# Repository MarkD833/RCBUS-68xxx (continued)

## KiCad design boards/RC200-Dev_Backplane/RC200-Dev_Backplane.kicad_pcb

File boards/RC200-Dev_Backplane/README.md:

# RCBus-80 Backplane

# Details
This is my offering of an RCBus-80 backplane. In the past I have used Steve Cousins SC701 6-slot backplanes for my boards. However, I found that at 6 slots, I might run out slots.

I had a chat with Steve to get his approval for me to take his SC701 backplane design and alter it for my own needs.

This backplane I've put together has 2 additional slots - making 8 in total. It also incorporates parts of Steve's SC719 digital I/O board to give 8 debug LEDs and 8 tactile pushbuttons. I also incorporated his SC729 CompactFlash module (with electronics by Tadeusz Pycio - www.vtsys.pl) as well.

The downside is that there is no expansion RCBus-80 connector to extend the bus further.

As well as combining Steve's SC701, SC719 and SC729 into one board, I've also added an LED driven by the /HALT signal buffered by one of the spare 74LS32 OR gates.

**NOTE** There is no voltage regulator on this board - an externally regulated 5V supply is required. Further, there is **NO** reverse polarity protection so check your power supply polarity.

# Board Assembly
Assembly of the board should be fairly straightforward. There are no surface mount devices to deal with.

Note regarding C18 - the capacitor is rather close to the pins that poke out the back of a board fitted to slot 8. Either use a standard height 100uF capacitor and bend the legs to 90 degrees so it sits horizontal to the board or use one of the lower profile capacitors that are around 7mm or 8mm tall.

Depending on your choice of LED colours, the associated current limiting resistor may need to be altered to give visually similar brightnesses.

# CompactFlash Adapter Header
The 2x20 header for the CompactFlash adapter can be a standard 2x20 0.1in (2.54mm) pin header or you can use a 2x20 shrouded IDC connector with ejector levers. The latter provides keying to avoid inserting the CompactFlash adapter the wrong way round and ejector levers to avoid bending pins.

# Jumpers
I have tried to replicate the jumper configurations that Steve provides on his SC701 so please refer to his documentation.

For my RCBus-68000, pinheaders J9..J22 should all have jumpers fitted to allow all signals to pass through. 

J23 should normally have a jumper fitted to connect the DS1233 reset signal to the backplane.

J24 can be used to provide an off-board reset switch if needed.
 
# Future Enhancements
+ Connect backplane D8..D15 to D8..D15 of the CompactFlash adapter to potentially allow for 16-bit data transfers.

# Errors
+ C18 - depending on the height of this capacitor, you may find it isn't possible to fully insert a board into the last backplane slot without bending the capacitor out of the way slightly.

# History
+ v1.0 - initial design

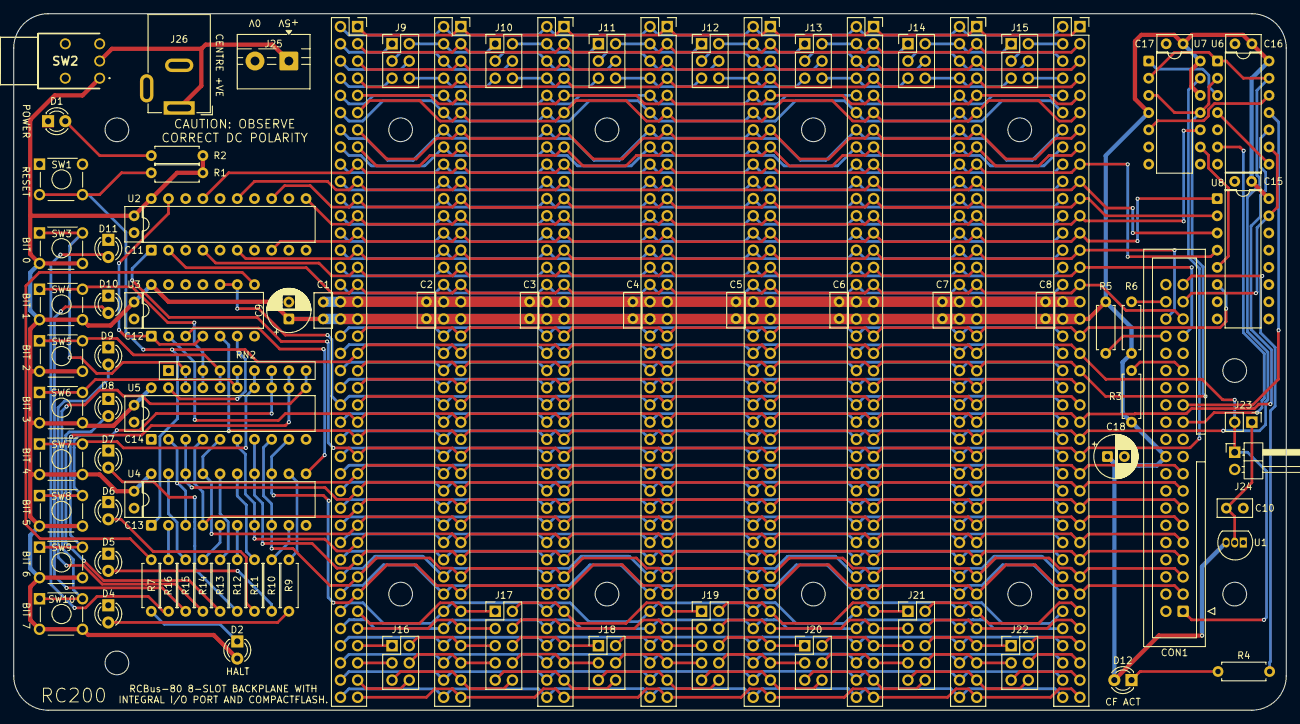
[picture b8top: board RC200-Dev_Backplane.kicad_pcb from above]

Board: 2 copper layers, 188.0 x 102.9 mm, 102 parts (0 on the bottom side), 170 nets.

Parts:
C1, C2, C3, C4, C5, C6, C7, C8, C11, C12, C13, C14, C15, C16, C17: 100n; C_Disc_D5.0mm_W2.5mm_P2.50mm
C9, C18: 100uF; CP_Radial_D6.3mm_P2.50mm
C10: 1n; C_Disc_D5.0mm_W2.5mm_P2.50mm
CON1: CONN_IDE_02x20; IDC-Header_2x20_P2.54mm_Vertical
D1, D2, D4, D5, D6, D7, D8, D9, D10, D11, D12: LED; LED_D3.0mm
H1, H2, H3, H4, H5, H6, H7, H8, H9, H10, H11, H12: MountingHole; MountingHole_3.5mm
J1, J2, J3, J4, J5, J6, J7, J8: Conn_02x40_Top_Bottom; PinSocket_2x40_P2.54mm_Vertical_Top_Bottom
J9, J10, J11, J12, J13, J14, J15, J16, J18, J20, J22: Conn_02x03_Odd_Even; PinHeader_2x03_P2.54mm_Vertical
J17, J19, J21: Conn_02x05_Odd_Even; PinHeader_2x05_P2.54mm_Vertical
J23: Conn_01x02; PinHeader_1x02_P2.54mm_Vertical
J24: Conn_01x02; PinHeader_1x02_P2.54mm_Horizontal
J25: Conn_01x02; TerminalBlock_MaiXu_MX126-5.0-02P_1x02_P5.00mm
J26: Barrel_Jack_Switch; BarrelJack_GCT_DCJ200-10-A_Horizontal
R1: 10K; R_Axial_DIN0207_L6.3mm_D2.5mm_P7.62mm_Horizontal
R2, R4, R7, R9, R10, R11, R12, R13, R14, R15, R16: 1K; R_Axial_DIN0207_L6.3mm_D2.5mm_P7.62mm_Horizontal
R3, R5, R6: 4K7; R_Axial_DIN0207_L6.3mm_D2.5mm_P7.62mm_Horizontal
RN2: 1K; R_Array_SIP9
SW1, SW3, SW4, SW5, SW6, SW7, SW8, SW9, SW10: SW_Push; SW_TH_Tactile
SW2: SW_SPDT; 2MS1T2B2M6QES
U1: DS1233-10; TO-92L_Inline
U2: 74HCT688; DIP-20_W7.62mm
U3, U6: 74LS32; DIP-14_W7.62mm
U4: 74HCT273; DIP-20_W7.62mm
U5: 74LS245; DIP-20_W7.62mm
U7: 74LS74; DIP-14_W7.62mm
U8: 74LS138; DIP-16_W7.62mm

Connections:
+5V: C1.1, C2.1, C3.1, C4.1, C5.1, C6.1, C7.1, C8.1, C9.1, C11.2, C12.2, C13.2, C14.2, C15.2, C16.2, C17.2, C18.1, CON1.20 (KEY), D2.2 (A), D12.2 (A), J1.18, J1.58, J2.18, J2.58, J3.18, J3.58, J4.18, J4.58, J5.18, J5.58, J6.18, J6.58, J7.18, J7.58, J8.18, J8.58, R1.1, R2.1, R3.1, R5.1, R6.1, SW2.1 (A), SW3.2, SW4.2, SW5.2, SW6.2, SW7.2, SW8.2, SW9.2, SW10.2, U1.3 (VCC), U2.20 (VCC), U3.14 (VCC), U4.20 (VCC), U5.20 (VCC), U6.14 (VCC), U7.4 (~S), U7.12 (D), U7.14 (VCC), U8.16 (VCC)
/A0: CON1.35 (DA0), J1.16, J2.16, J3.16, J4.16, J5.16, J6.16, J7.16, J8.16, U2.2 (P0)
/A1: CON1.33 (DA1), J1.15, J2.15, J3.15, J4.15, J5.15, J6.15, J7.15, J8.15, U2.4 (P1)
/A2: CON1.36 (DA2), J1.14, J2.14, J3.14, J4.14, J5.14, J6.14, J7.14, J8.14, U2.6 (P2)
/A3: J1.13, J2.13, J3.13, J4.13, J5.13, J6.13, J7.13, J8.13, U2.8 (P3), U8.1 (A0)
/A4: J1.12, J2.12, J3.12, J4.12, J5.12, J6.12, J7.12, J8.12, U2.11 (P4), U7.10 (~S)
/A5: J1.11, J2.11, J3.11, J4.11, J5.11, J6.11, J7.11, J8.11, U2.13 (P5), U8.2 (A1)
/A6: J1.10, J2.10, J3.10, J4.10, J5.10, J6.10, J7.10, J8.10, U2.15 (P6), U8.3 (A2)
/A7: J1.9, J2.9, J3.9, J4.9, J5.9, J6.9, J7.9, J8.9, U2.17 (P7), U8.4 (E1)
/A8: J1.8, J2.8, J3.8, J4.8, J5.8, J6.8, J7.8, J8.8
/A9: J1.7, J2.7, J3.7, J4.7, J5.7, J6.7, J7.7, J8.7
/A10: J1.6, J2.6, J3.6, J4.6, J5.6, J6.6, J7.6, J8.6
/A11: J1.5, J2.5, J3.5, J4.5, J5.5, J6.5, J7.5, J8.5
/A12: J1.4, J2.4, J3.4, J4.4, J5.4, J6.4, J7.4, J8.4
/A13: J1.3, J2.3, J3.3, J4.3, J5.3, J6.3, J7.3, J8.3
/A14: J1.2, J2.2, J3.2, J4.2, J5.2, J6.2, J7.2, J8.2
/A15: J1.1, J2.1, J3.1, J4.1, J5.1, J6.1, J7.1, J8.1
/A16: J1.56, J2.56, J3.56, J4.56, J5.56, J6.56, J7.56, J8.56
/A17: J1.55, J2.55, J3.55, J4.55, J5.55, J6.55, J7.55, J8.55
/A18: J1.54, J2.54, J3.54, J4.54, J5.54, J6.54, J7.54, J8.54
/A19: J1.53, J2.53, J3.53, J4.53, J5.53, J6.53, J7.53, J8.53
/A20: J1.52, J2.52, J3.52, J4.52, J5.52, J6.52, J7.52, J8.52
/A21: J1.51, J2.51, J3.51, J4.51, J5.51, J6.51, J7.51, J8.51
/A22: J1.50, J2.50, J3.50, J4.50, J5.50, J6.50, J7.50, J8.50
/A23: J1.49, J2.49, J3.49, J4.49, J5.49, J6.49, J7.49, J8.49
/CLK: J1.21, J2.21, J3.21, J4.21, J5.21, J6.21, J7.21, J8.21, U6.2, U7.3 (C), U7.11 (C)
/CLK2: J1.61, J2.61, J3.61, J4.61, J5.61, J6.61, J7.61, J8.61
/D0: CON1.17 (D0), J1.27, J2.27, J3.27, J4.27, J5.27, J6.27, J7.27, J8.27, U4.3 (D0), U5.2 (A0)
/D1: CON1.15 (D1), J1.28, J2.28, J3.28, J4.28, J5.28, J6.28, J7.28, J8.28, U4.18 (D7), U5.3 (A1)
/D2: CON1.13 (D2), J1.29, J2.29, J3.29, J4.29, J5.29, J6.29, J7.29, J8.29, U4.4 (D1), U5.4 (A2)
/D3: CON1.11 (D3), J1.30, J2.30, J3.30, J4.30, J5.30, J6.30, J7.30, J8.30, U4.17 (D6), U5.5 (A3)
/D4: CON1.9 (D4), J1.31, J2.31, J3.31, J4.31, J5.31, J6.31, J7.31, J8.31, U4.7 (D2), U5.6 (A4)
/D5: CON1.7 (D5), J1.32, J2.32, J3.32, J4.32, J5.32, J6.32, J7.32, J8.32, U4.14 (D5), U5.7 (A5)
/D6: CON1.5 (D6), J1.33, J2.33, J3.33, J4.33, J5.33, J6.33, J7.33, J8.33, U4.8 (D3), U5.8 (A6)
/D7: CON1.3 (D7), J1.34, J2.34, J3.34, J4.34, J5.34, J6.34, J7.34, J8.34, U4.13 (D4), U5.9 (A7)
/D8: J1.67, J2.67, J3.67, J4.67, J5.67, J6.67, J7.67, J8.67
/D9: J1.68, J2.68, J3.68, J4.68, J5.68, J6.68, J7.68, J8.68
/D10: J1.69, J2.69, J3.69, J4.69, J5.69, J6.69, J7.69, J8.69
/D11: J1.70, J2.70, J3.70, J4.70, J5.70, J6.70, J7.70, J8.70
/D12: J1.71, J2.71, J3.71, J4.71, J5.71, J6.71, J7.71, J8.71
/D13: J1.72, J2.72, J3.72, J4.72, J5.72, J6.72, J7.72, J8.72
/D14: J1.73, J2.73, J3.73, J4.73, J5.73, J6.73, J7.73, J8.73
/D15: J1.74, J2.74, J3.74, J4.74, J5.74, J6.74, J7.74, J8.74
/HALT_LED: R7.2, U3.8
/PAGE: J1.60, J2.60, J3.60, J4.60, J5.60, J6.60, J7.60, J8.60
/PB1: RN2.2 (R1), SW3.1, U5.18 (B0)
/PB2: RN2.3 (R2), SW4.1, U5.17 (B1)
/PB3: RN2.4 (R3), SW5.1, U5.16 (B2)
/PB4: RN2.5 (R4), SW6.1, U5.15 (B3)
/PB5: RN2.6 (R5), SW7.1, U5.14 (B4)
/PB6: RN2.7 (R6), SW8.1, U5.13 (B5)
/PB7: RN2.8 (R7), SW9.1, U5.12 (B6)
/PB8: RN2.9 (R8), SW10.1, U5.11 (B7)
/RX2: J1.76, J2.76, J3.76, J4.76, J5.76, J6.76, J7.76, J8.76
/RX_A: J1.36, J2.36, J17.3
/RX_B: J3.36, J4.36, J17.4, J19.3
/RX_C: J5.36, J6.36, J19.4, J21.3
/RX_D: J7.36, J8.36, J21.4
/TX2: J1.75, J2.75, J3.75, J4.75, J5.75, J6.75, J7.75, J8.75
/TX_A: J1.35, J2.35, J17.1
/TX_B: J3.35, J4.35, J17.2, J19.1
/TX_C: J5.35, J6.35, J19.2, J21.1
/TX_D: J7.35, J8.35, J21.2
/n37_a: J1.37, J16.1
/n37_b: J2.37, J16.2, J17.5
/n37_c: J3.37, J17.6, J18.1
/n37_d: J4.37, J18.2, J19.5
/n37_e: J5.37, J19.6, J20.1
/n37_f: J6.37, J20.2, J21.5
/n37_g: J7.37, J21.6, J22.1
/n37_h: J8.37, J22.2
/n38_a: J1.38, J16.3
/n38_b: J2.38, J16.4, J17.7
/n38_c: J3.38, J17.8, J18.3
/n38_d: J4.38, J18.4, J19.7
/n38_e: J5.38, J19.8, J20.3
/n38_f: J6.38, J20.4, J21.7
/n38_g: J7.38, J21.8, J22.3
/n38_h: J8.38, J22.4
/n39_a: J1.39, J16.6
/n39_b: J2.39, J16.5, J17.10
/n39_c: J3.39, J17.9, J18.6
/n39_d: J4.39, J18.5, J19.10
/n39_e: J5.39, J19.9, J20.6
/n39_f: J6.39, J20.5, J21.10
/n39_g: J7.39, J21.9, J22.6
/n39_h: J8.39, J22.5
/n40: J1.40, J2.40, J3.40, J4.40, J5.40, J6.40, J7.40, J8.40
/n41: J1.41, J2.41, J3.41, J4.41, J5.41, J6.41, J7.41, J8.41
/n42_a: J1.42, J9.1
/n42_b: J2.42, J9.2, J10.1
/n42_c: J3.42, J10.2, J11.1
/n42_d: J4.42, J11.2, J12.1
/n42_e: J5.42, J12.2, J13.1
/n42_f: J6.42, J13.2, J14.1
/n42_g: J7.42, J14.2, J15.1
/n42_h: J8.42, J15.2
/n43_a: J1.43, J9.4
/n43_b: J2.43, J9.3, J10.4
/n43_c: J3.43, J10.3, J11.4
/n43_d: J4.43, J11.3, J12.4
/n43_e: J5.43, J12.3, J13.4
/n43_f: J6.43, J13.3, J14.4
/n43_g: J7.43, J14.3, J15.4
/n43_h: J8.43, J15.3
/n44_a: J1.44, J9.5
/n44_b: J2.44, J9.6, J10.5
/n44_c: J3.44, J10.6, J11.5
/n44_d: J4.44, J11.6, J12.5
/n44_e: J5.44, J12.6, J13.5
/n44_f: J6.44, J13.6, J14.5
/n44_g: J7.44, J14.6, J15.5
/n44_h: J8.44, J15.6
/n45: J1.45, J2.45, J3.45, J4.45, J5.45, J6.45, J7.45, J8.45
/n46: J1.46, J2.46, J3.46, J4.46, J5.46, J6.46, J7.46, J8.46
/n47: J1.47, J2.47, J3.47, J4.47, J5.47, J6.47, J7.47, J8.47
/n48: J1.48, J2.48, J3.48, J4.48, J5.48, J6.48, J7.48, J8.48
/n77: J1.77, J2.77, J3.77, J4.77, J5.77, J6.77, J7.77, J8.77
/n78: J1.78, J2.78, J3.78, J4.78, J5.78, J6.78, J7.78, J8.78
/n79: J1.79, J2.79, J3.79, J4.79, J5.79, J6.79, J7.79, J8.79
/n80: J1.80, J2.80, J3.80, J4.80, J5.80, J6.80, J7.80, J8.80
/~BUSAK: J1.62, J2.62, J3.62, J4.62, J5.62, J6.62, J7.62, J8.62
/~BUSRQ: J1.64, J2.64, J3.64, J4.64, J5.64, J6.64, J7.64, J8.64
/~CS_CF: CON1.37 (~CS1FX), U6.9, U8.15 (O0)
/~HALT: J1.63, J2.63, J3.63, J4.63, J5.63, J6.63, J7.63, J8.63, U3.9, U3.10
/~INT: J1.22, J2.22, J3.22, J4.22, J5.22, J6.22, J7.22, J8.22
/~IORD: CON1.25 (~DIOR), U6.11
/~IORQ: J1.26, J2.26, J3.26, J4.26, J5.26, J6.26, J7.26, J8.26, U2.1 (G), U7.13 (~R)
/~IOWR: CON1.23 (~DIOW), U6.6
/~M1: J1.19, J2.19, J3.19, J4.19, J5.19, J6.19, J7.19, J8.19, U8.6 (E3)
/~MREQ: J1.23, J2.23, J3.23, J4.23, J5.23, J6.23, J7.23, J8.23
/~NMI: J1.66, J2.66, J3.66, J4.66, J5.66, J6.66, J7.66, J8.66
/~RD: J1.25, J2.25, J3.25, J4.25, J5.25, J6.25, J7.25, J8.25, U3.5, U6.1, U6.13, U7.2 (D)
/~RESET: CON1.1 (~RESET), J1.20, J2.20, J3.20, J4.20, J5.20, J6.20, J7.20, J8.20, J23.2, J24.1, R1.2, SW1.2, U4.1 (~Mr)
/~RFSH: J1.59, J2.59, J3.59, J4.59, J5.59, J6.59, J7.59, J8.59
/~WAIT: J1.65, J2.65, J3.65, J4.65, J5.65, J6.65, J7.65, J8.65
/~WR: J1.24, J2.24, J3.24, J4.24, J5.24, J6.24, J7.24, J8.24, U3.2, U6.10
GND: C1.2, C2.2, C3.2, C4.2, C5.2, C6.2, C7.2, C8.2, C9.2, C10.2, C11.1, C12.1, C13.1, C14.1, C15.1, C16.1, C17.1, C18.2, CON1.2 (GND), CON1.19 (GND), CON1.22 (GND), CON1.24 (GND), CON1.26 (GND), CON1.30 (GND), CON1.40 (GND), D1.1 (K), D4.1 (K), D5.1 (K), D6.1 (K), D7.1 (K), D8.1 (K), D9.1 (K), D10.1 (K), D11.1 (K), J1.17, J1.57, J2.17, J2.57, J3.17, J3.57, J4.17, J4.57, J5.17, J5.57, J6.17, J6.57, J7.17, J7.57, J8.17, J8.57, J24.2, J25.2, J26.2, J26.3, RN2.1 (common), SW1.1, U1.1 (GND), U2.3 (R0), U2.5 (R1), U2.7 (R2), U2.9 (R3), U2.10 (GND), U2.12 (R4), U2.14 (R5), U2.16 (R6), U2.18 (R7), U3.7 (GND), U3.12, U3.13, U4.10 (GND), U5.1 (A->B), U5.10 (GND), U6.5, U6.7 (GND), U7.7 (GND), U8.8 (GND)
unnamed: CON1.38 (~CS3FX), R6.2
unnamed: CON1.39 (~DASP), R4.2
unnamed: CON1.29 (~DMACK), R3.2
unnamed: CON1.34 (~PDIAG), R5.2
unnamed: D1.2 (A), R2.2
unnamed: D2.1 (K), R7.1
unnamed: D4.2 (A), R9.2
unnamed: D5.2 (A), R10.2
unnamed: D6.2 (A), R11.2
unnamed: D7.2 (A), R12.2
unnamed: D8.2 (A), R13.2
unnamed: D9.2 (A), R14.2
unnamed: D10.2 (A), R15.2
unnamed: D11.2 (A), R16.2
unnamed: D12.1 (K), R4.1
unnamed: C10.1, J23.1, U1.2 (~RESET)
unnamed: J25.1, J26.1, SW2.2 (B)
unnamed: U2.19 (P=R), U3.1, U3.4
unnamed: U3.3, U4.11 (Cp)
unnamed: R16.1, U4.2 (Q0)
unnamed: R14.1, U4.5 (Q1)
unnamed: R12.1, U4.6 (Q2)
unnamed: R10.1, U4.9 (Q3)
unnamed: R9.1, U4.12 (Q4)
unnamed: R11.1, U4.15 (Q5)
unnamed: R13.1, U4.16 (Q6)
unnamed: R15.1, U4.19 (Q7)
unnamed: U3.6, U5.19 (CE)
unnamed: U6.4, U6.8
unnamed: U6.12, U7.5 (Q)
unnamed: U6.3, U7.1 (~R)
unnamed: U7.9 (Q), U8.5 (E2)

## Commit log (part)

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2025-02-16 added board images
2025-02-16 extension issues
2025-02-24 Added PCB files etc
2025-02-24 Oops
2025-03-04 Updated progress
2025-03-05 Added new boards
2025-03-08 added monitor and code samples
2025-03-08 updated code readme
2025-03-08 updated SC129 text
2025-03-08 fixed link error
2025-03-10 added SC704 test code
2025-03-10 added SC705 code
2025-03-10 minor text update
2025-04-25 introduce CP/M68K v1.3
2025-04-25 corrected diskdefs
2025-05-04 Lots of updates
2025-05-04 Forgot to mention EhBASIC
2025-05-10 Update to v2 board set
    Lots of updates to reflect the new v2 boards that use the full RCBus 80 pins as well as slight modifications to the various test programs to reflect the new IO and MEM space addresses.
2025-05-10 Broken link to images
2025-05-12 Added details of SC611
2025-05-16 updated readme's
2025-05-24 software
    renamed the assembler code directory and added in the c code directory
2025-05-25 update C demo code
2025-05-25 Create LICENSE
2025-06-05 Added TMS9918A updates
2025-06-07 update demo code
    Tidy up the ASCII demo and introduce the Nyan Cat bitmap animation demo.
2025-06-20 Updated TMS9918A demos
    Demo updates and addition of the sprite demo.
2025-06-20 Update README.md
    Added sprites demo text.
2025-07-03 Added C code of ASCII demo
2025-07-03 typo
2025-07-04 updated setup instructions
2025-07-07 Added sprites C demo
2025-07-07 Added Nyan cat demo
2025-07-10 Added fern demo code
2025-07-11 Reorganised documentation
    Reorganised documentation and added comments in TMS library.
2025-07-11 update image links
2025-08-05 added MC68901 demo code
2025-08-05 added MFP serial echo
2025-08-05 minor updates
2025-08-14 added MC68302
2025-08-15 more 68302 details
2025-08-21 add new rom/ram board
2025-08-22 Update to readme
2025-08-22 update parts list
2025-08-22 Updated pinout list and boards readme
2025-08-22 added note re clock on 68230
2025-08-23 added 68230 PI/T information
2025-09-13 update to PIO board and 68302 board notes
2025-10-05 Reformat readme
2025-10-26 Added BOMs for each board
2025-10-29 Updated board readme files.
2025-11-01 Updated BOMs and added gerber files for all boards.
2025-11-01 68000 clock
    Added details of the 68000 board clock frequencies used.
2025-11-06 Added V9958A demonstrations
    Based around Dean Netherton's HDMI for RC board.
2025-11-06 minor corrections
2025-11-19 Corrections to RCBus pinout
    Corrected nDTACK pin.
    Deleted nINT3.
    Moved nINT2 to pin 38.
2025-11-29 Added 68302 ROM monitor code
2025-12-07 Changed readme from plain test to Markdown
2025-12-07 Add comment to 68000 CPU about CPU Orientation
2025-12-07 Convert Serial card Readme from plain text to Markdown
2025-12-07 Added some jumper settting details to the serial card Readme
2025-12-07 Change Serial readme from plain text to Markdown
2025-12-07 Corrections to missing tracks
2025-12-07 Add some jumper settings to serial Readme
2025-12-07 Converted PIO readme to Markdown
2025-12-07 Convert MFP Readme to Markdown
2025-12-07 Convered ROM_RAM_2 board Readme to Markdown
2025-12-08 Updated some board readme's
2025-12-08 Updated board readme's
2025-12-09 updated rom/ram board #2 schematic notes
2025-12-09 update readme's and added s-record file
    68302 readme updated
    s-rec file containing MON68Kv1.3, CP/M, CP/M BIOS and EhBASIC.
2025-12-09 updated 68302 readme
2025-12-10 updated 68000 board readme
2025-12-12 update readme's
2025-12-12 updated various readme's
2025-12-14 Annotated schematic with notes on errors found so far.
2025-12-14 added SPI master board
2025-12-14 Updated schematics
2025-12-14 spelling errors
2025-12-16 updated readme's and added LBE board
2025-12-26 Extended baud rate details for the Philips devices.
2025-12-26 Added LBE board details etc
2025-12-27 Change method of monitor variable definitions
    With some assemblers (e.g. Vasm) the previous method of using "ORG xxxx" and
    <var> ds.b <N>
    forces the assembler to fill the blank between the end of the code and the ORG
    statement
    Changing the definitions to be just "EQU"s doesn't force the aseembler to
    fill in the blank.
2025-12-27 Remove spurious spaces after commas
    Some assemblers (e.g. vasm) don't like a space after a comma in mnemonics
    This commit removes spaces after commas in mnemonics only (i.e. not in comments!)
2025-12-27 Changed PC-relative assembly syntax to modern Motorola style.
    The code was written in an older style of:
    lea bemsg1(PC),a0
    to:
    lea (bemsg1,PC),A0
    which is accepted by more modern assemblers (e.g. vasm)
2025-12-27 Add conditional assembly for Vasm
    Easy68k and Vasm use different methods to ensure alignment. Easy68k uses:
    ORG (*+1)&-2
    Whereas Vasm uses:
    align 2
2026-01-07 Added note re 68681 X2 pin
2026-01-08 updated MON68K to support 115200 baud
2026-01-08 Added note re IRQ2 setting
2026-01-14 Update README.md
    Added note re issues with ehBasic running on v1.4 of rcMON68K.
2026-01-15 Corrected serial comms fault
2026-01-17 Added SIO & MATHS board
2026-01-18 updated readme with more board designs
2026-01-18 Updated address ranges for new boards
2026-01-25 Updated LBE board details
2026-02-12 Updated readme's for LBE #2
2026-02-15 Removed LBE #2
2026-02-16 Corrected spelling
2026-03-07 updated SPI board details
2026-03-07 corrected typo
2026-03-14 notes re series 2 boards
2026-03-14 can't spell!
2026-03-14 Added series 2 boards and images
2026-03-14 added more board details
2026-03-16 added details of 68302 ROM/RAM swap monitor
2026-03-17 corrected images
2026-03-28 Reorganise and rename boards
2026-03-28 updated RCBus pinout
2026-03-28 correction to command line
2026-04-08 reorganise c code folder
2026-04-08 added libc, libm, crt0 and SC611 demo
2026-04-08 added SC704 I2C scanner
2026-04-08 added SC704 read & write demo
2026-04-08 added TMS9918A ASCII chars demo
2026-04-08 Added TMS9918A demos
2026-04-08 Added V9958 demos
2026-04-08 Added V9958 demo
2026-06-15 updated rcMON68K
2026-06-15 added s-records
2026-06-15 spelling error(s)
2026-06-16 minor doc changes
